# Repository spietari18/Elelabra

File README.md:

## BL50A0503 - Elektroniikan laboratoriotyöt 1

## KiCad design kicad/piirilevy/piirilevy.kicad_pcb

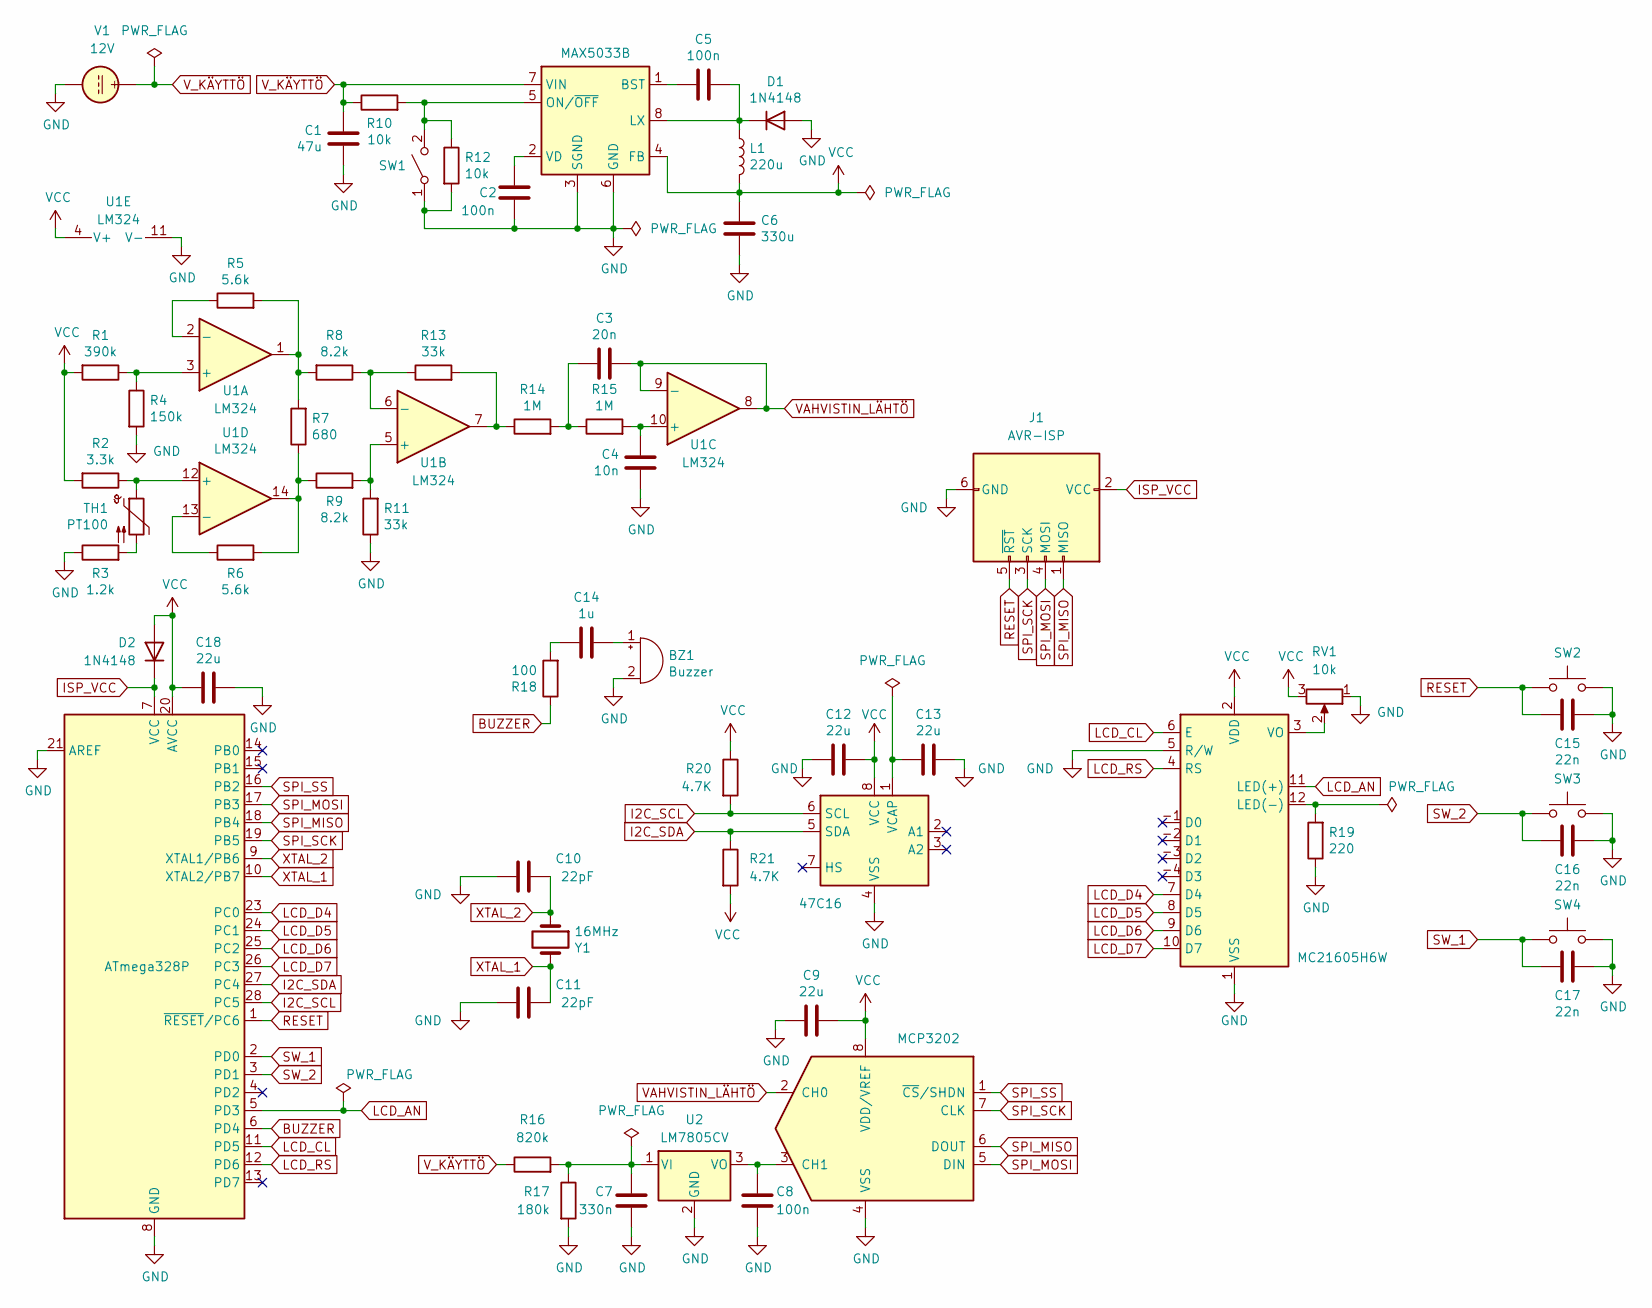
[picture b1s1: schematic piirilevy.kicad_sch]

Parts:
BZ1: Buzzer; PinHeader_1x02_P2.54mm_Vertical
C1: 47u; C_Radial_D6.3mm_H5.0mm_P2.50mm
C2, C5, C8: 100n; C_Disc_D4.3mm_W1.9mm_P5.00mm
C3: 20n; C_Disc_D4.3mm_W1.9mm_P5.00mm
C4: 10n; C_Disc_D4.3mm_W1.9mm_P5.00mm
C6: 330u; C_Radial_D8.0mm_H7.0mm_P3.50mm
C7: 330n; C_Disc_D4.3mm_W1.9mm_P5.00mm
C9, C18: 22u; C_Radial_D5.0mm_H7.0mm_P2.00mm
C10, C11: 22pF; C_Disc_D4.3mm_W1.9mm_P5.00mm
C12, C13: 22u; C_Radial_D5.0mm_H5.0mm_P2.00mm
C14: 1u; C_Radial_D5.0mm_H5.0mm_P2.00mm
C15, C16, C17: 22n; C_Disc_D4.3mm_W1.9mm_P5.00mm
D1, D2: 1N4148; D_DO-35_SOD27_P7.62mm_Horizontal
DS1: MC21605H6W; PinHeader_1x12_P2.54mm_Vertical
J1: AVR-ISP; PinHeader_2x03_P2.54mm_Vertical
L1: 220u; C_Radial_D8.0mm_H7.0mm_P3.50mm
R1: 390k; R_Axial_DIN0204_L3.6mm_D1.6mm_P7.62mm_Horizontal
R2: 3.3k; R_Axial_DIN0204_L3.6mm_D1.6mm_P7.62mm_Horizontal
R3: 1.2k; R_Axial_DIN0204_L3.6mm_D1.6mm_P7.62mm_Horizontal
R4: 150k; R_Axial_DIN0204_L3.6mm_D1.6mm_P7.62mm_Horizontal
R5, R6: 5.6k; R_Axial_DIN0204_L3.6mm_D1.6mm_P7.62mm_Horizontal
R7: 680; R_Axial_DIN0204_L3.6mm_D1.6mm_P7.62mm_Horizontal
R8, R9: 8.2k; R_Axial_DIN0204_L3.6mm_D1.6mm_P7.62mm_Horizontal
R10, R12: 10k; R_Axial_DIN0204_L3.6mm_D1.6mm_P7.62mm_Horizontal
R11, R13: 33k; R_Axial_DIN0204_L3.6mm_D1.6mm_P7.62mm_Horizontal
R14, R15: 1M; R_Axial_DIN0204_L3.6mm_D1.6mm_P7.62mm_Horizontal
R16: 820k; R_Axial_DIN0204_L3.6mm_D1.6mm_P7.62mm_Horizontal
R17: 180k; R_Axial_DIN0204_L3.6mm_D1.6mm_P7.62mm_Horizontal
R18: 100; R_Axial_DIN0204_L3.6mm_D1.6mm_P7.62mm_Horizontal
R19: 220; R_Axial_DIN0204_L3.6mm_D1.6mm_P7.62mm_Horizontal
R20, R21: 4.7K; R_Axial_DIN0204_L3.6mm_D1.6mm_P7.62mm_Horizontal
RV1: 10k; Potentiometer_Vishay_T73YP_Vertical
SW1: SW_SPST; PinHeader_1x02_P2.54mm_Vertical
SW2, SW3, SW4: SW_Push; PinHeader_1x02_P2.54mm_Vertical
TH1: PT100; PinHeader_1x02_P2.54mm_Vertical
U1: LM324; DIP-14_W7.62mm_LongPads
U2: LM7805CV; TO-220-3_Horizontal_TabDown
U3: ATmega328P; DIP-28_W7.62mm_LongPads
U4: MAX5033B; DIP-8_W7.62mm_LongPads
U5: MCP3202; DIP-8_W7.62mm_LongPads
U6: 47C16; DIP-8_W7.62mm_LongPads
V1: 12V; PinHeader_1x02_P2.54mm_Vertical
Y1: 16MHz; Crystal_HC18-U_Vertical

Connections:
BUZZER: R18.1, U3.6 (PD4)
GND: BZ1.2 (+), C1.1, C2.2, C4.2, C6.2, C7.2, C8.2, C9.2, C10.1, C11.2, C12.2, C13.1, C15.1, C16.1, C17.1, C18.1, D1.2 (A), DS1.1 (VSS), DS1.5 (R/W), J1.6 (GND), R3.1, R4.2, R11.1, R12.2, R17.2, R19.1, RV1.1, SW1.1 (A), SW2.2, SW3.2, SW4.2, U1.11 (V-), U2.2 (GND), U3.8 (GND), U3.21 (AREF), U3.22 (GND), U4.3 (SGND), U4.6 (GND), U5.4 (VSS), U6.4 (VSS), V1.2
I2C_SCL: R20.2, U3.28 (PC5), U6.6 (SCL)
I2C_SDA: R21.1, U3.27 (PC4), U6.5 (SDA)
ISP_VCC: D2.1 (K), J1.2 (VCC), U3.7 (VCC)
LCD_AN: DS1.11 (LED(+)), U3.5 (PD3)
LCD_CL: DS1.6 (E), U3.11 (PD5)
LCD_D4: DS1.7 (D4), U3.23 (PC0)
LCD_D5: DS1.8 (D5), U3.24 (PC1)
LCD_D6: DS1.9 (D6), U3.25 (PC2)
LCD_D7: DS1.10 (D7), U3.26 (PC3)
LCD_RS: DS1.4 (RS), U3.12 (PD6)
unnamed: BZ1.1 (-), C14.2
unnamed: C2.1, U4.2 (VD)
unnamed: C3.1, R14.2, R15.1
unnamed: C4.1, R15.2, U1.10 (+)
unnamed: C5.1, D1.1 (K), L1.1, U4.8 (LX)
unnamed: C5.2, U4.1 (BST)
unnamed: C7.1, R16.2, R17.1, U2.1 (VI)
unnamed: C8.1, U2.3 (VO), U5.3 (CH1)
unnamed: C13.2, U6.1 (VCAP)
unnamed: C14.1, R18.2
unnamed: DS1.3 (VO), RV1.2
unnamed: DS1.12 (LED(-)), R19.2
unnamed: R1.1, R4.1, U1.3 (+)
unnamed: R2.1, TH1.1, U1.12 (+)
unnamed: R3.2, TH1.2
unnamed: R5.1, U1.2 (-)
unnamed: R5.2, R7.2, R8.2, U1.1
unnamed: R6.1, U1.13 (-)
unnamed: R6.2, R7.1, R9.1, U1.14
unnamed: R10.2, R12.1, SW1.2 (B), U4.5 (ON/~OFF)
unnamed: R9.2, R11.2, U1.5 (+)
unnamed: R8.1, R13.1, U1.6 (-)
unnamed: R13.2, R14.1, U1.7
RESET: C15.2, J1.5 (~RST), SW2.1, U3.1 (~RESET/PC6)
SPI_MISO: J1.1 (MISO), U3.18 (PB4), U5.6 (DOUT)
SPI_MOSI: J1.4 (MOSI), U3.17 (PB3), U5.5 (DIN)
SPI_SCK: J1.3 (SCK), U3.19 (PB5), U5.7 (CLK)
SPI_SS: U3.16 (PB2), U5.1 (~CS/SHDN)
SW_1: C17.2, SW4.1, U3.2 (PD0)
SW_2: C16.2, SW3.1, U3.3 (PD1)
VAHVISTIN_LÄHTÖ: C3.2, U1.8, U1.9 (-), U5.2 (CH0)
VCC: C6.1, C9.1, C12.1, C18.2, D2.2 (A), DS1.2 (VDD), L1.2, R1.2, R2.2, R20.1, R21.2, RV1.3, U1.4 (V+), U3.20 (AVCC), U4.4 (FB), U5.8 (VDD/VREF), U6.8 (VCC)
V_KÄYTTÖ: C1.2, R10.1, R16.1, U4.7 (VIN), V1.1
XTAL_1: C11.1, U3.10 (XTAL2/PB7), Y1.2
XTAL_2: C10.2, U3.9 (XTAL1/PB6), Y1.1

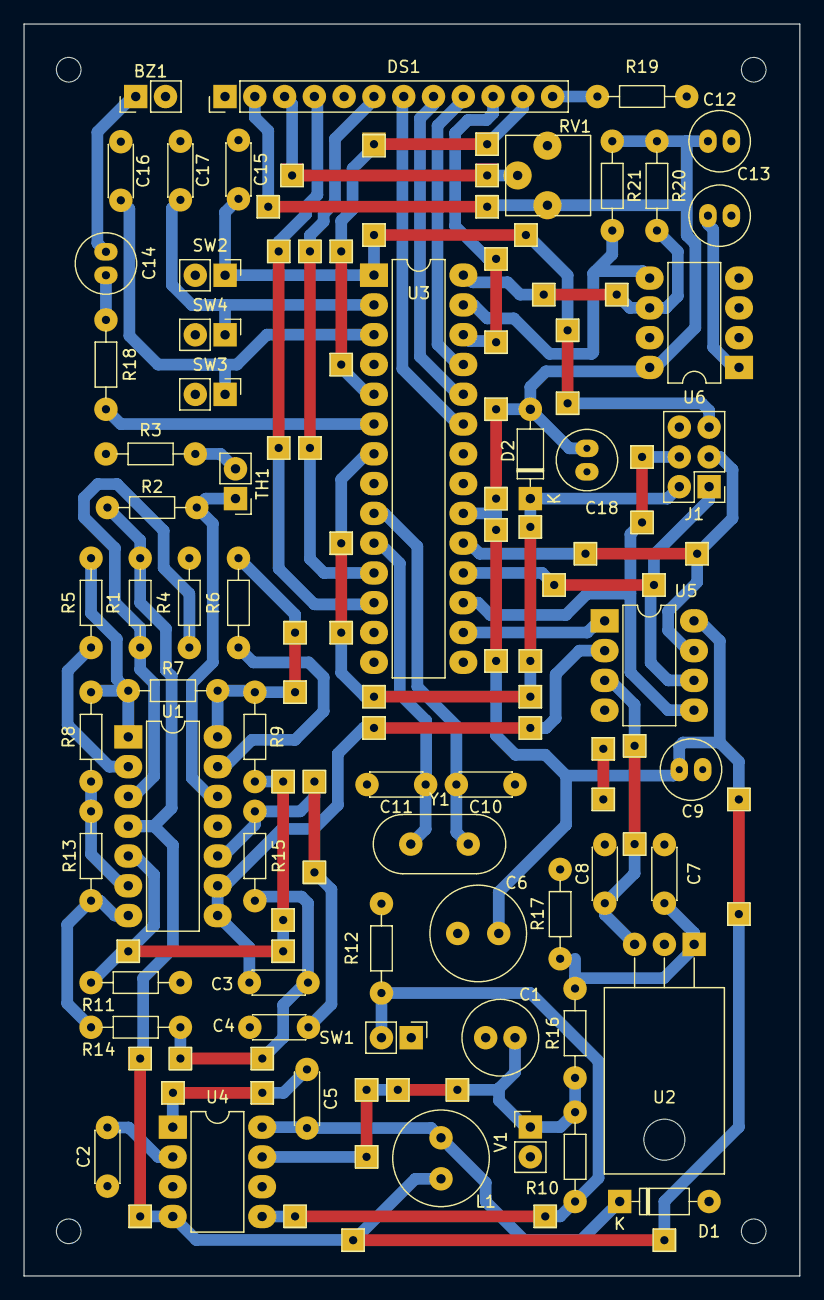
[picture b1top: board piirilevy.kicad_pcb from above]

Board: 2 copper layers, 66.2 x 106.8 mm, 63 parts (0 on the bottom side), 47 nets.

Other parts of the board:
H1, H1#2, H3, H4: MountingHole_2.1mm

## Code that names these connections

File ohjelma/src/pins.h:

#ifndef PINS_H
#define PINS_H

#include "macro.h"

/* SPI pinnit */
DEFINE_PIN(SPI_SS,   B, 2); // PB2
DEFINE_PIN(SPI_CLK,  B, 5); // PB5
DEFINE_PIN(SPI_MOSI, B, 3); // PB3
DEFINE_PIN(SPI_MISO, B, 4); // PB4

/* I2C pinnit */
DEFINE_PIN(I2C_SDA, C, 4); // PC4
DEFINE_PIN(I2C_SCL, C, 5); // PC5

#if 1
/* LCD näyttö. */
DEFINE_PIN(_LCD_RS, D, 6); // PD6
DEFINE_PIN(_LCD_EN, D, 5); // PD5
DEFINE_PIN(_LCD_B5, C, 0); // PC0
DEFINE_PIN(_LCD_B6, C, 1); // PC1
DEFINE_PIN(_LCD_B7, C, 2); // PC2
DEFINE_PIN(_LCD_B8, C, 3); // PC3

/* Summeri. */
DEFINE_PIN(BUZZER, D, 4); // PD4

/* LCD:n taustavalon anodi. */
DEFINE_PIN(LCD_AN, D, 3); // PD3

/* Napit. */
DEFINE_PIN(BTN_LT, D, 1); // PD1, (vasen)
DEFINE_PIN(BTN_RT, D, 0); // PD1, (oikea)
#else
/* LCD näyttö. */
DEFINE_PIN(_LCD_RS, C, 0); // PC0, (A0)
DEFINE_PIN(_LCD_EN, C, 1); // PC1, (A1)
DEFINE_PIN(_LCD_B5, C, 2); // PC2, (A2)
DEFINE_PIN(_LCD_B6, C, 3); // PC3, (A3)
DEFINE_PIN(_LCD_B7, D, 4); // PC4, (A4)
DEFINE_PIN(_LCD_B8, D, 5); // PC5, (A5)

/* Summeri. */
DEFINE_PIN(BUZZER, D, 3); // PD3, (D3)

/* LCD:n taustavalon anodi. */
DEFINE_PIN(LCD_AN, D, 2); // PD2, (D2)

/* Napit. */
DEFINE_PIN(BTN_RT, D, 1); // PD1, (D1) (vasen)
DEFINE_PIN(BTN_LT, D, 0); // PD0, (D0) (oikea)
#endif

#endif // !PINS_H

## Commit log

2021-11-17 Lähdekoodi + Ohjelmointiympäristö
2021-11-17 Lisää README.md
2021-11-17 Siirrä liitteet omaan kansioonsa.
2021-11-17 Lisää muutoksia.
2021-11-17 Poista alamoduulit.
2021-11-17 Lisää kirjastot.
2021-11-18 Jännitejakajalaskin.
2021-11-24 Muutoksia.
2021-11-24 Keskiviikon muutokset.
2021-11-24 Lisää .gitignore
2021-11-25 Koodin parantelua.
2021-11-25 Pieni korjaus LCD koodiin.
2021-11-25 Lisää korjauksia.
2021-11-25 Korjaukset että ohjelma kääntyy.
2021-11-25 Nyt tämä kääntyy.
2021-11-26 memcpy() pituudet kuntoon
2021-11-26 Perjantain muutokset.
2021-11-26 Pientä parantelua.
2021-11-26 Korjaa virhe nappien testikoodissa.
2021-11-30 Jaa liitteet kansioihin.
2021-11-30 AD-muunnos lähdekoodi liite
2021-11-30 Add files via upload
    Kuva kytkennästä
2021-11-30 Päivitä liitteet
2021-11-30 Päivitä liitteet/README.md
2021-12-08 Parannuksia koodiin, posta sprintf() kokonaan.
2021-12-09 More features.
2021-12-09 Pieniä korjauksia.
2021-12-09 Ohjelman jako tiedostoihin.
2021-12-09 Vanha koodi talteen.
2021-12-11 Lisää koodi summerille ja taustavalon välkytykselle.
2021-12-11 Käyttöliittymäkoodin parantelua + muutamia korjauksia.
2021-12-14 Käyttöliittymä liitteet.
2021-12-14 Muutoksia liitteisiin.
2021-12-14 Valikkokoodin muutoksia + muuta.
2021-12-15 Jotain.
2021-12-15 Jotain. v.2
2021-12-15 Poista riippuvuus Arduino kirjastoista kokonaan.
2021-12-16 Päivityksiä kääntötyökaluun.
2021-12-16 Korjaa LCD koodi + poista turhat esikääntäjädirektiivit.
2021-12-16 Muutamia korjauksia, jotta laite toimii.
2021-12-16 Poista a.out ja lisää a.out gitignoreen.
2021-12-16 Valikon uudelleensuunnittelu.
2021-12-16 Ja heti korjauksia perään.
2021-12-21 KiCad tiedostot.
2022-01-12 EERAM funktiot + muuta.
2022-01-12 Heti korjauksia perään.
2022-01-13 Torstain muutokset.
2022-01-19 Muutokset kaavioihin.
2022-01-27 Piirilevylle KiCad projekti.
2022-01-27 Muutokset piirilevyyn.
2022-01-27 Testausreititys piirilevylle.
2022-02-02 Käyttöliittymän parantelua.
2022-02-02 Lisää parantelua käyttöliittymään.
2022-02-02 Poista vimin paskatiedostot.
2022-02-02 kicad muutokset
2022-02-04 Korjaukset piirilevyyn + CNC tiedostot ja kuvat.
2022-02-04 3D kuva piirilevystä.
2022-02-06 Korjauksia.
2022-02-11 koodia
2022-02-16 Yksipuoleinen piirilevy.
2022-02-23 Muutamia korjauksia.
2022-03-14 PNS pisteiden ja asetusten luku EERAM:ista + muuta
2022-03-14 Muutamia korjauksia perään.
2022-03-14 Laske uudet PNS kertoimet kun pisteet luetaan EERAM:ista.
2022-03-15 Tiistain muutokset.
2022-03-16 Pientä koodin siivousta, datapisteiden katselu CALIBRATION valikkoon ja muistin testaus OPTIONS valikkoon.
2022-03-16 Korjaukset o_memtest() funktioon perään.
2022-03-16 Lisää msg_* funktioihin piippaus.
2022-03-16 Korjaa lämpötilalukeman päivitys CALIBRATION valikossa.
2022-03-16 Muokkaa alarm.c:tä paremmaksi, lisää alkutune (DOOM E1M1).
2022-03-16 Korja kirjoitusvirhe.
2022-03-19 Jotain
2022-03-19 Lopulliset korjaukset.
